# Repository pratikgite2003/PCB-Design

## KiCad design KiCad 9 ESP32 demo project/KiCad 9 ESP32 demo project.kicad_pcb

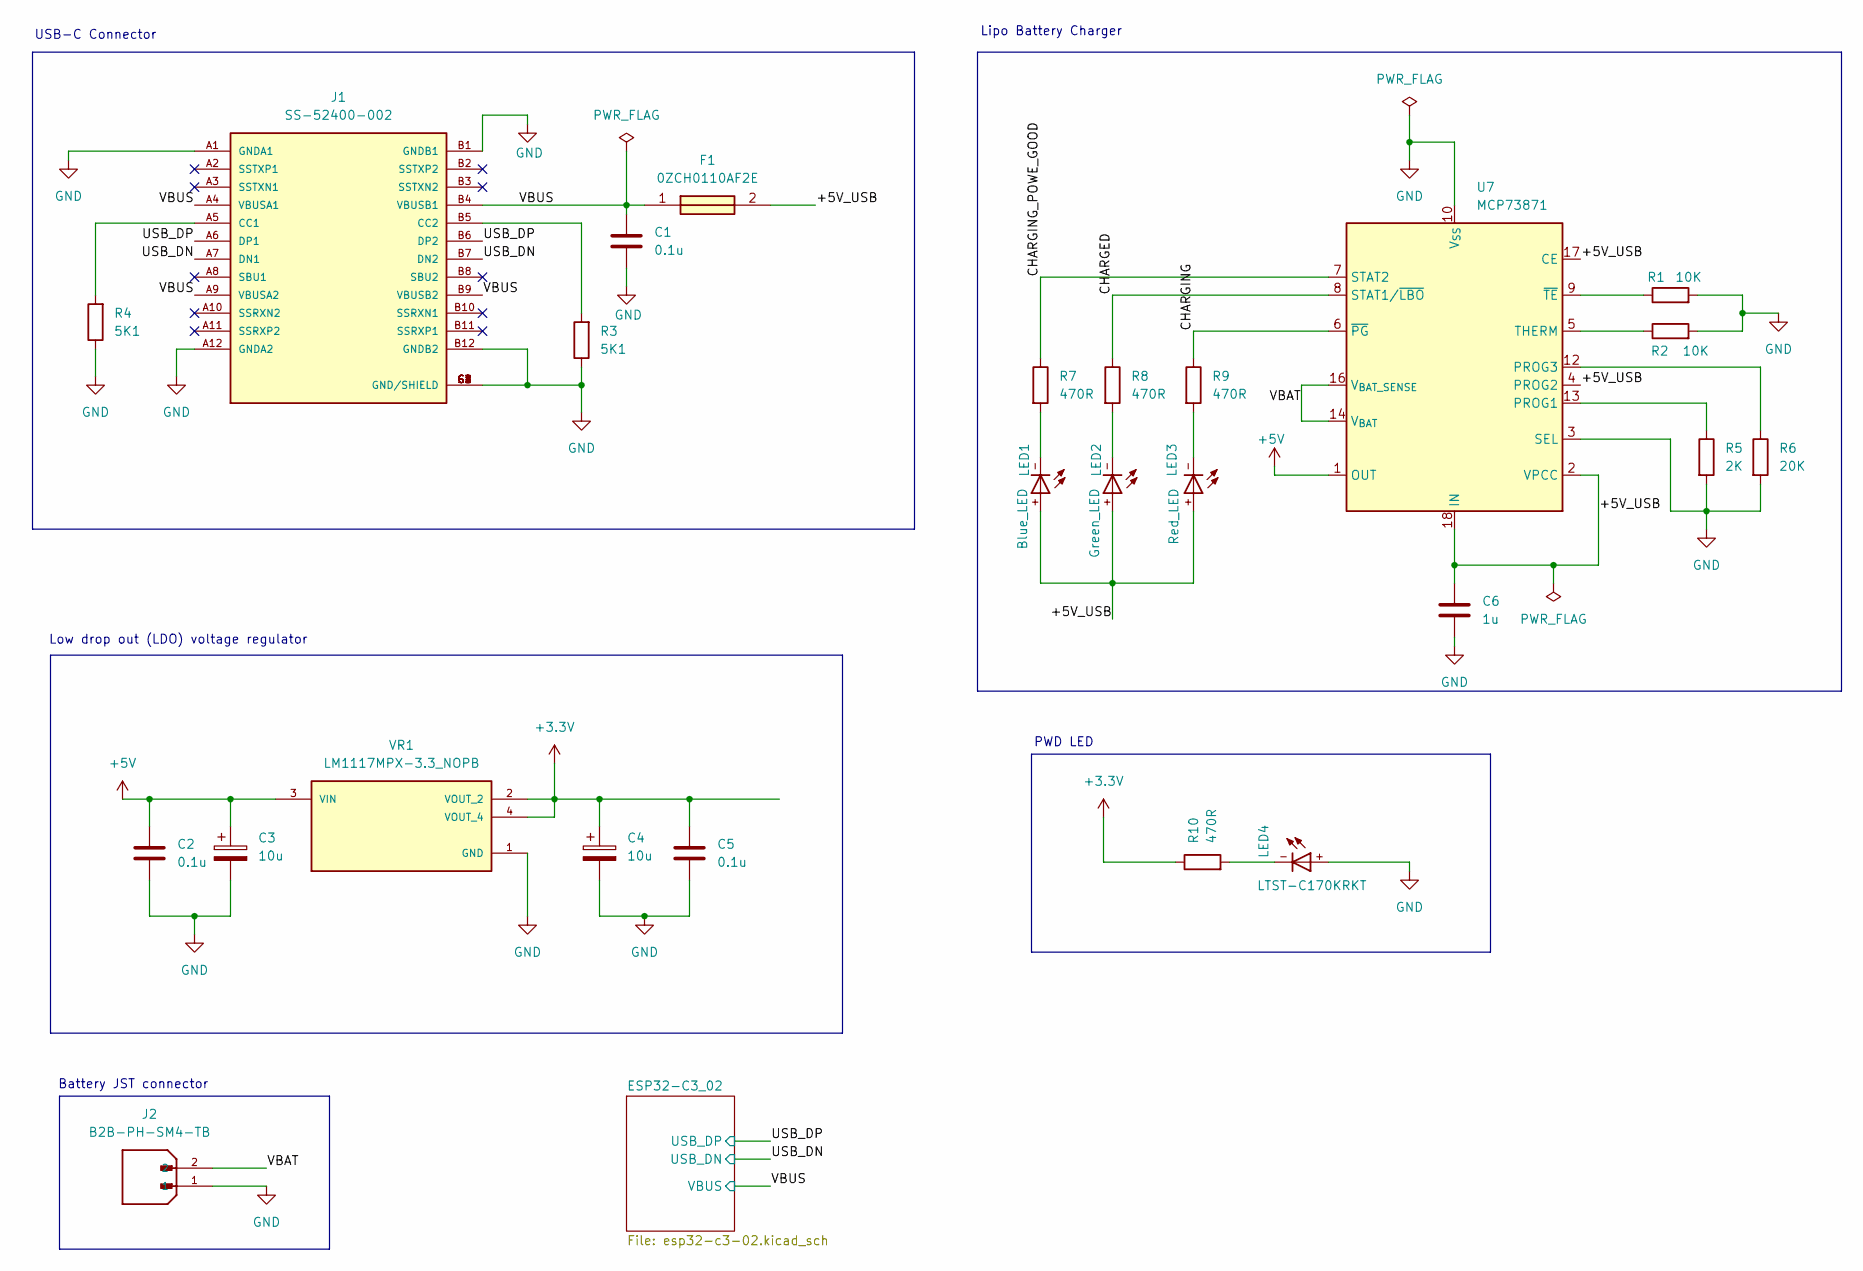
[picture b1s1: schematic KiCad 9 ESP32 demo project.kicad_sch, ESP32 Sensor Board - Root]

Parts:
C1, C2, C5: 0.1u; C_0805_2012Metric
C3, C4: 10u; CAPC3216X110N
C6: 1u; C_0805_2012Metric
F1: 0ZCH0110AF2E; FUSC3226X100N; Manufacturer_Part_Number 0ZCH0110AF2E
J1: SS-52400-002; BELFUSE_SS-52400-002; PARTREV A0
J2: B2B-PH-SM4-TB; JST_B2B-PH-SM4-TB; PARTREV N/A
LED1: Blue_LED; DIOC200X125X110
LED2: Green_LED; DIOC200X125X110
LED3: Red_LED; DIOC200X125X110
LED4: LTST-C170KRKT; DIOC200X125X110
R1, R2: 10K; R_0805_2012Metric
R3, R4: 5K1; R_0805_2012Metric
R5: 2K; R_0805_2012Metric
R6: 20K; R_0805_2012Metric
R7, R8, R9, R10: 470R; R_0805_2012Metric
U7: MCP73871; QFN-20-1EP_4x4mm_P0.5mm_EP2.5x2.5mm
VR1: LM1117MPX-3.3_NOPB; VREG_LM1117MPX-3.3_NOPB; PARTREV O

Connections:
+3.3V: C4.1, C5.1, R10.1, VR1.2 (VOUT_2), VR1.4 (VOUT_4); also elsewhere on the board
+5V: C2.1, C3.1, U7.1 (OUT), U7.20 (OUT), VR1.3 (VIN)
/+5V_USB: C6.1, F1.2, LED1.+, LED2.+, LED3.+, U7.2 (VPCC), U7.4 (PROG2), U7.17 (CE), U7.18 (IN), U7.19 (IN)
/CHARGED: R8.1, U7.8 (STAT1/~LBO)
/CHARGING: R9.1, U7.6 (~PG)
/CHARGING_POWE_GOOD: R7.1, U7.7 (STAT2)
/USB_DN: J1.A7 (DN1), J1.B7 (DN2); also elsewhere on the board
/USB_DP: J1.A6 (DP1), J1.B6 (DP2); also elsewhere on the board
/VBAT: J2.2, U7.14 (V_{BAT}), U7.15 (V_{BAT}), U7.16 (V_{BAT_SENSE})
/VBUS: C1.1, F1.1, J1.A4 (VBUSA1), J1.A9 (VBUSA2), J1.B4 (VBUSB1), J1.B9 (VBUSB2); also elsewhere on the board
GND: C1.2, C2.2, C3.2, C4.2, C5.2, C6.2, J1.A1 (GNDA1), J1.A12 (GNDA2), J1.B1 (GNDB1), J1.B12 (GNDB2), J1.G1 (GND/SHIELD), J1.G2 (GND/SHIELD), J1.G3 (GND/SHIELD), J1.G4 (GND/SHIELD), J1.S1 (GND/SHIELD), J1.S2 (GND/SHIELD), J1.S3 (GND/SHIELD), J1.S4 (GND/SHIELD), J2.1, LED4.+, R1.2, R2.2, R3.1, R4.1, R5.2, R6.2, U7.3 (SEL), U7.10 (V_{SS}), U7.11 (V_{SS}), U7.21 (V_{SS}), VR1.1 (GND); also elsewhere on the board
unnamed: J1.A5 (CC1), R4.2
unnamed: J1.B5 (CC2), R3.2
unnamed: LED1.-, R7.2
unnamed: LED2.-, R8.2
unnamed: LED3.-, R9.2
unnamed: LED4.-, R10.2
unnamed: R5.1, U7.13 (PROG1)
unnamed: R6.1, U7.12 (PROG3)
unnamed: R2.1, U7.5 (THERM)
unnamed: R1.1, U7.9 (~TE)

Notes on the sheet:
Lipo Battery Charger
Low drop out (LDO) voltage regulator
PWD LED
Battery JST connector
USB-C Connector

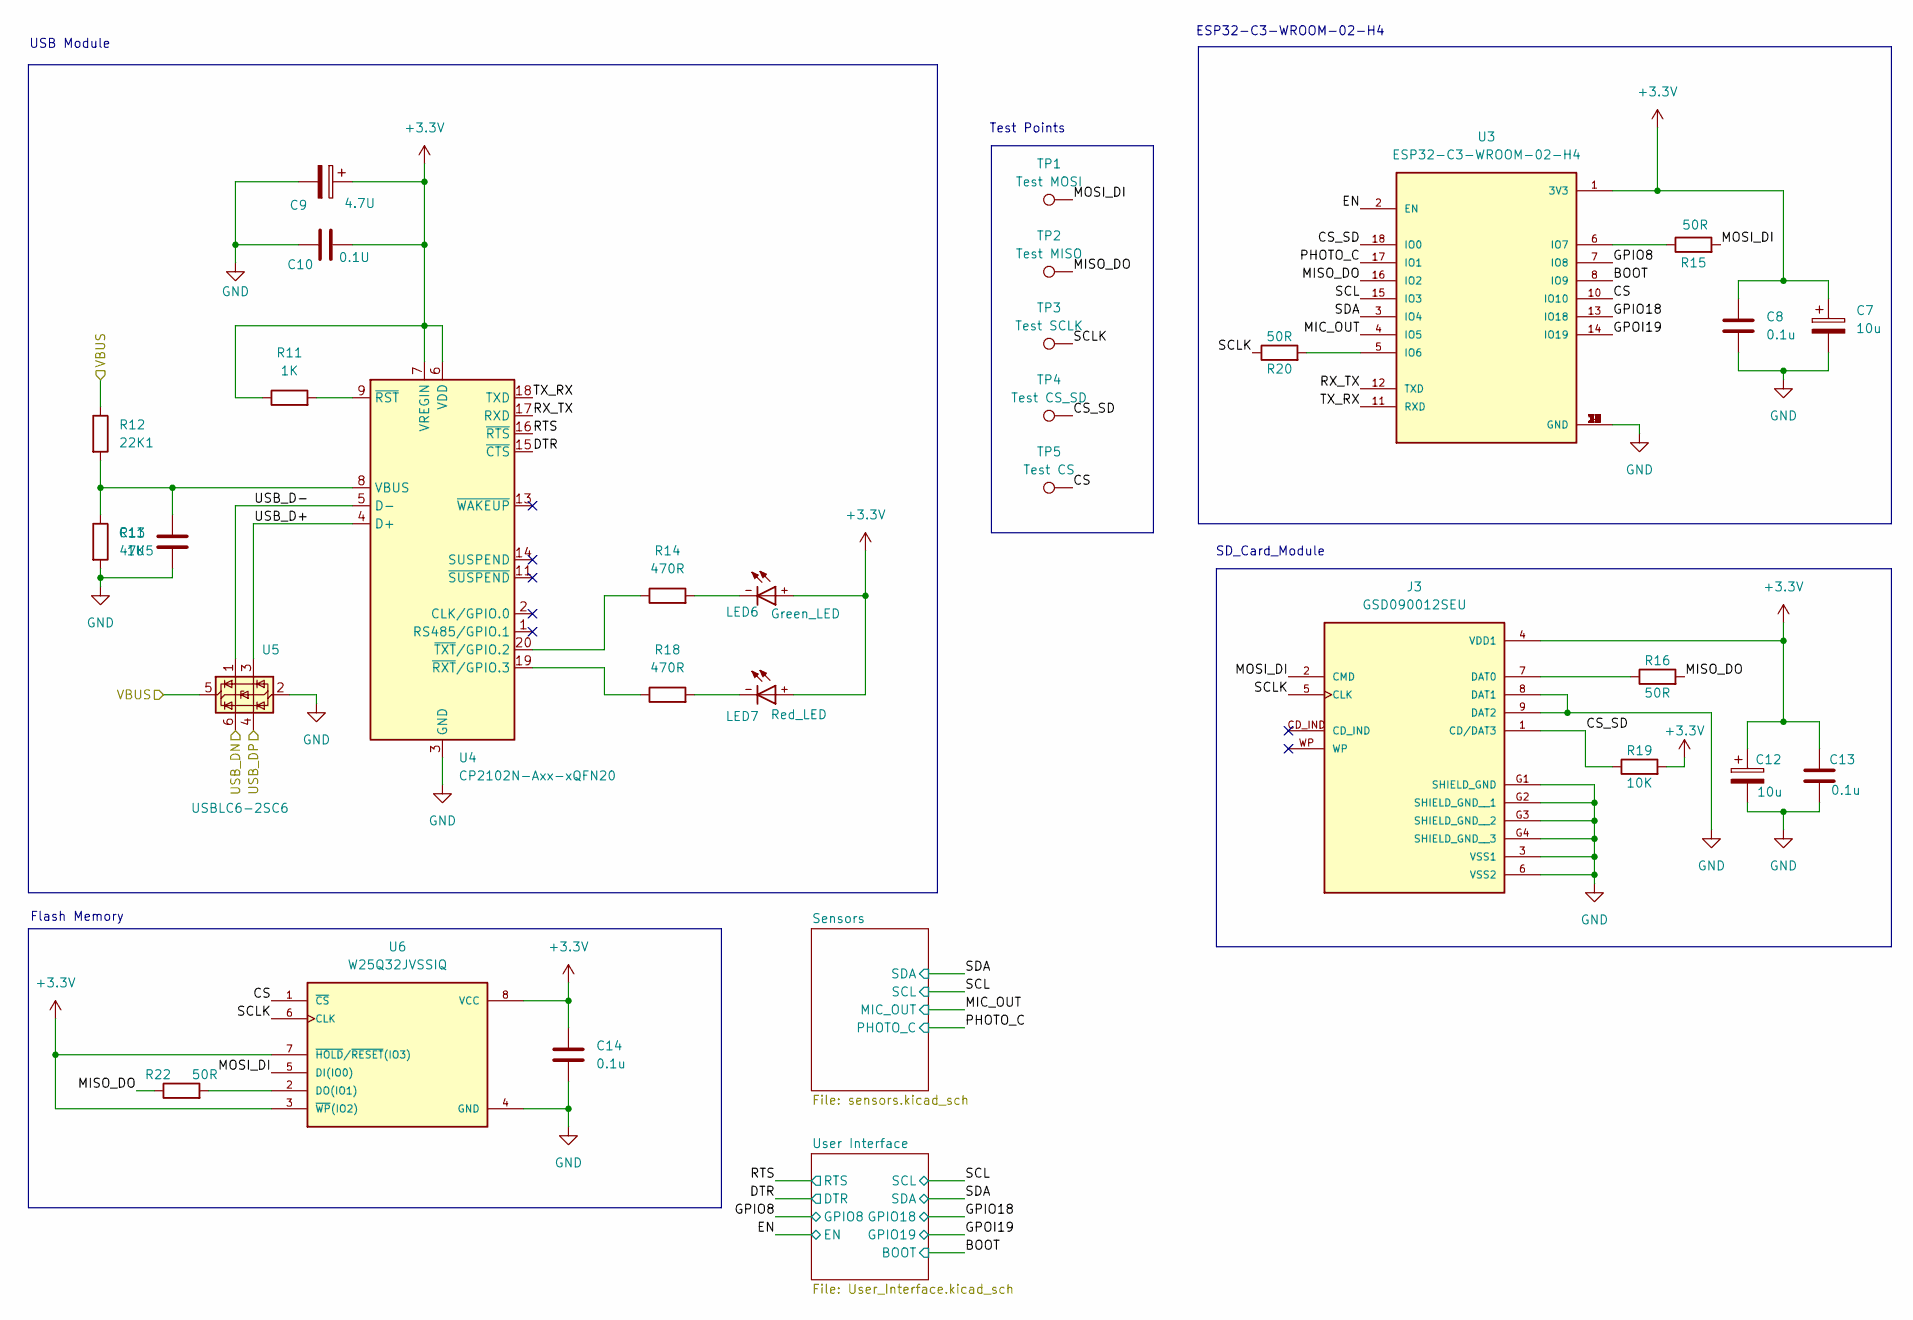
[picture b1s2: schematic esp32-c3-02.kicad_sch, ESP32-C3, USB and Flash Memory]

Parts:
C7: 10u; CAPC3216X110N
C8, C13, C14: 0.1u; C_0805_2012Metric
C9: 4.7U; CAPC3216X110N
C10: 0.1U; C_0805_2012Metric
C11: 1U; C_0805_2012Metric
C12: 10u; C_0805_2012Metric
J3: GSD090012SEU; AMPHENOL_GSD090012SEU; PARTREV E
LED6: Green_LED; DIOC200X125X110
LED7: Red_LED; DIOC200X125X110
R11: 1K; R_0805_2012Metric
R12: 22K1; R_0805_2012Metric
R13: 47K5; R_0805_2012Metric
R14, R18: 470R; R_0805_2012Metric
R15, R16, R20, R22: 50R; R_0805_2012Metric
R19: 10K; R_0805_2012Metric
TP1: Test MOSI; TestPoint_Pad_D1.0mm
TP2: Test MISO; TestPoint_Pad_D1.0mm
TP3: Test SCLK; TestPoint_Pad_D1.0mm
TP4: Test CS_SD; TestPoint_Pad_D1.0mm
TP5: Test CS; TestPoint_Pad_D1.0mm
U3: ESP32-C3-WROOM-02-H4; MODULE_ESP32-C3-WROOM-02-H4
U4: CP2102N-Axx-xQFN20; SiliconLabs_QFN-20-1EP_3x3mm_P0.5mm_EP1.8x1.8mm
U5: USBLC6-2SC6; SOT-23-6
U6: W25Q32JVSSIQ; SOIC127P790X216-8N; M_PART_NUMBER W25QXX

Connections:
+3.3V: C7.1, C8.1, C9.1, C10.2, C12.1, C13.1, C14.1, J3.4 (VDD1), LED6.+, LED7.+, R11.1, R19.2, U3.1 (3V3), U4.6 (VDD), U4.7 (VREGIN), U6.3 (~WP(IO2)), U6.7 (~HOLD/~RESET(IO3)), U6.8 (VCC); also elsewhere on the board
/ESP32-C3_02/BOOT: U3.8 (IO9); also elsewhere on the board
/ESP32-C3_02/CS: TP5.1, U3.10 (IO10), U6.1 (~CS)
/ESP32-C3_02/CS_SD: J3.1 (CD/DAT3), R19.1, TP4.1, U3.18 (IO0)
/ESP32-C3_02/DTR: U4.15 (~CTS); also elsewhere on the board
/ESP32-C3_02/EN: U3.2 (EN); also elsewhere on the board
/ESP32-C3_02/GPIO8: U3.7 (IO8); also elsewhere on the board
/ESP32-C3_02/GPIO18: U3.13 (IO18); also elsewhere on the board
/ESP32-C3_02/GPOI19: U3.14 (IO19); also elsewhere on the board
/ESP32-C3_02/MIC_OUT: U3.4 (IO5); also elsewhere on the board
/ESP32-C3_02/MISO_DO: R16.2, R22.1, TP2.1, U3.16 (IO2)
/ESP32-C3_02/MOSI_DI: J3.2 (CMD), R15.2, TP1.1, U6.5 (DI(IO0))
/ESP32-C3_02/PHOTO_C: U3.17 (IO1); also elsewhere on the board
/ESP32-C3_02/RTS: U4.16 (~RTS); also elsewhere on the board
/ESP32-C3_02/RX_TX: U3.12 (TXD), U4.17 (RXD)
/ESP32-C3_02/SCL: U3.15 (IO3); also elsewhere on the board
/ESP32-C3_02/SCLK: J3.5 (CLK), R20.1, TP3.1, U6.6 (CLK)
/ESP32-C3_02/SDA: U3.3 (IO4); also elsewhere on the board
/ESP32-C3_02/TX_RX: U3.11 (RXD), U4.18 (TXD)
/ESP32-C3_02/USB_D+: U4.4 (D+), U5.3 (I/O2)
/ESP32-C3_02/USB_D-: U4.5 (D-), U5.1 (I/O1)
/USB_DN: U5.6 (I/O1); also elsewhere on the board
/USB_DP: U5.4 (I/O2); also elsewhere on the board
/VBUS: R12.1, U5.5 (VBUS); also elsewhere on the board
GND: C7.2, C8.2, C9.2, C10.1, C11.2, C12.2, C13.2, C14.2, J3.3 (VSS1), J3.6 (VSS2), J3.8 (DAT1), J3.9 (DAT2), J3.G1 (SHIELD_GND), J3.G2 (SHIELD_GND__1), J3.G3 (SHIELD_GND__2), J3.G4 (SHIELD_GND__3), R13.2, U3.9 (GND), U3.19 (GND), U3.20 (GND), U3.21 (GND), U3.22 (GND), U3.23 (GND), U3.24 (GND), U3.25 (GND), U3.26 (GND), U3.27 (GND), U3.28 (GND), U3.29 (GND), U3.30 (GND), U3.31 (GND), U3.32 (GND), U3.33 (GND), U3.34 (GND), U3.35 (GND), U3.36 (GND), U3.37 (GND), U3.38 (GND), U3.39 (GND), U4.3 (GND), U4.12 (GND), U4.21 (GND), U5.2 (GND), U6.4 (GND); also elsewhere on the board
unnamed: J3.7 (DAT0), R16.1
unnamed: LED6.-, R14.2
unnamed: LED7.-, R18.2
unnamed: R20.2, U3.5 (IO6)
unnamed: R15.1, U3.6 (IO7)
unnamed: C11.1, R12.2, R13.1, U4.8 (VBUS)
unnamed: R11.2, U4.9 (~RST)
unnamed: R18.1, U4.19 (~RXT/GPIO.3)
unnamed: R14.1, U4.20 (~TXT/GPIO.2)
unnamed: R22.2, U6.2 (DO(IO1))

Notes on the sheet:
Test Points
USB Module
Flash Memory
ESP32-C3-WROOM-02-H4
SD_Card_Module

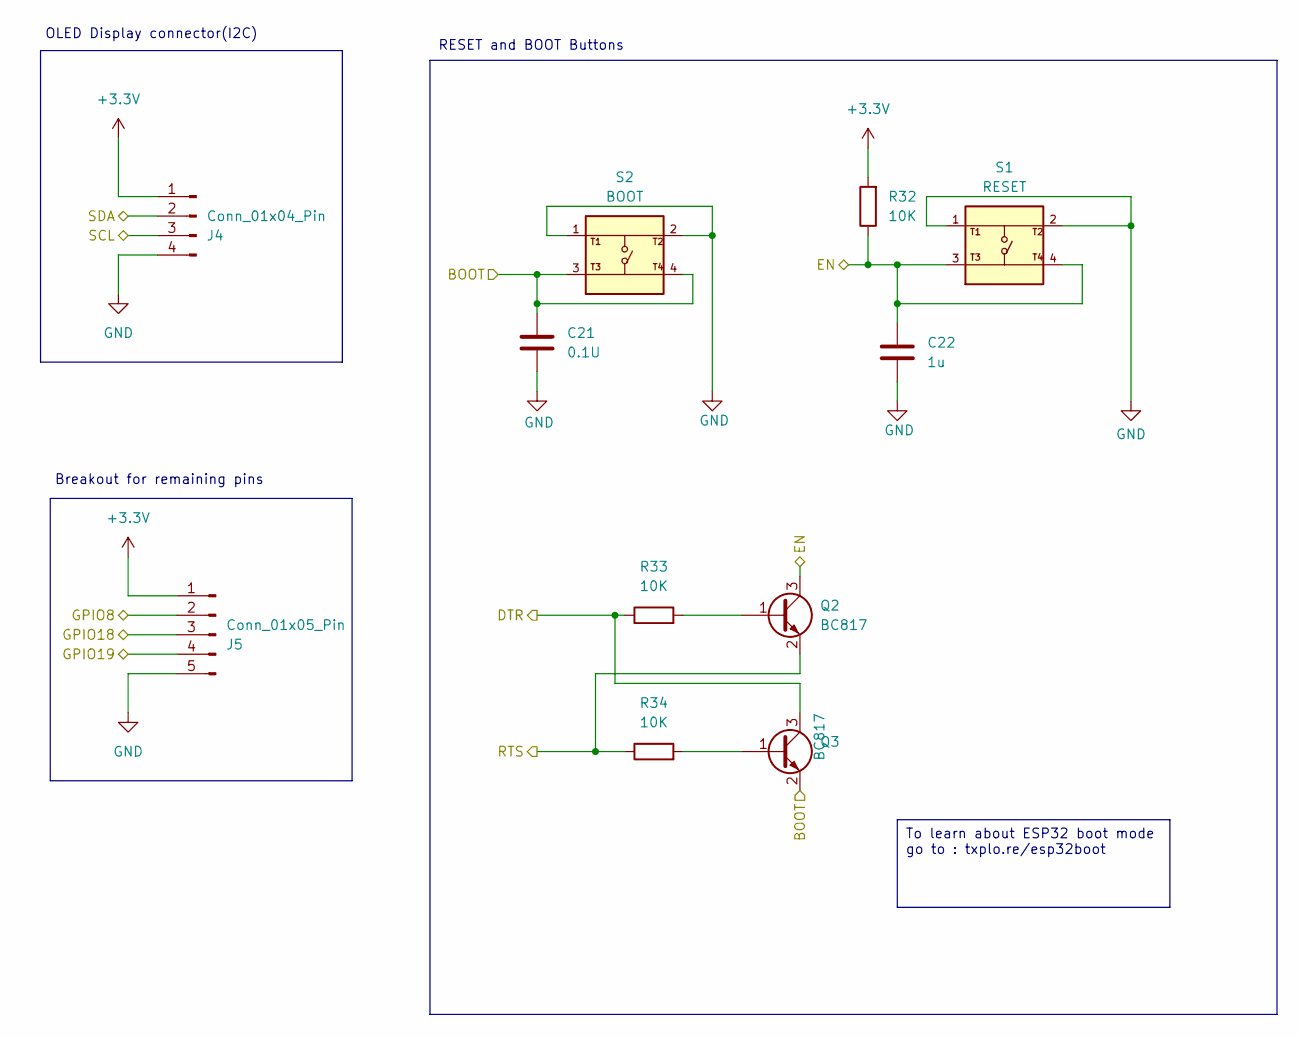
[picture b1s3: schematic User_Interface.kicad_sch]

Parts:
C21: 0.1U; C_0805_2012Metric
C22: 1u; C_0805_2012Metric
J4: Conn_01x04_Pin; PinHeader_1x04_P2.54mm_Vertical
J5: Conn_01x05_Pin; PinHeader_1x05_P2.54mm_Vertical
Q2, Q3: BC817; SOT95P230X110-3N
R32, R33, R34: 10K; R_0805_2012Metric
S1: RESET; SW_USLPT2819DT2TR; PARTREV P
S2: BOOT; SW_USLPT2819DT2TR; PARTREV P

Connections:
+3.3V: J4.1, J5.1, R32.2; also elsewhere on the board
/ESP32-C3_02/BOOT: C21.1, Q3.2 (E), S2.3, S2.4; also elsewhere on the board
/ESP32-C3_02/DTR: Q3.3 (C), R33.1; also elsewhere on the board
/ESP32-C3_02/EN: C22.1, Q2.3 (C), R32.1, S1.3, S1.4; also elsewhere on the board
/ESP32-C3_02/GPIO8: J5.2; also elsewhere on the board
/ESP32-C3_02/GPIO18: J5.3; also elsewhere on the board
/ESP32-C3_02/GPOI19: J5.4; also elsewhere on the board
/ESP32-C3_02/RTS: Q2.2 (E), R34.1; also elsewhere on the board
/ESP32-C3_02/SCL: J4.3; also elsewhere on the board
/ESP32-C3_02/SDA: J4.2; also elsewhere on the board
GND: C21.2, C22.2, J4.4, J5.5, S1.1, S1.2, S2.1, S2.2; also elsewhere on the board
unnamed: Q2.1 (B), R33.2
unnamed: Q3.1 (B), R34.2

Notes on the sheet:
To learn about ESP32 boot mode go to : txplo.re/esp32boot
Breakout for remaining pins
RESET and BOOT Buttons
OLED Display connector(I2C)

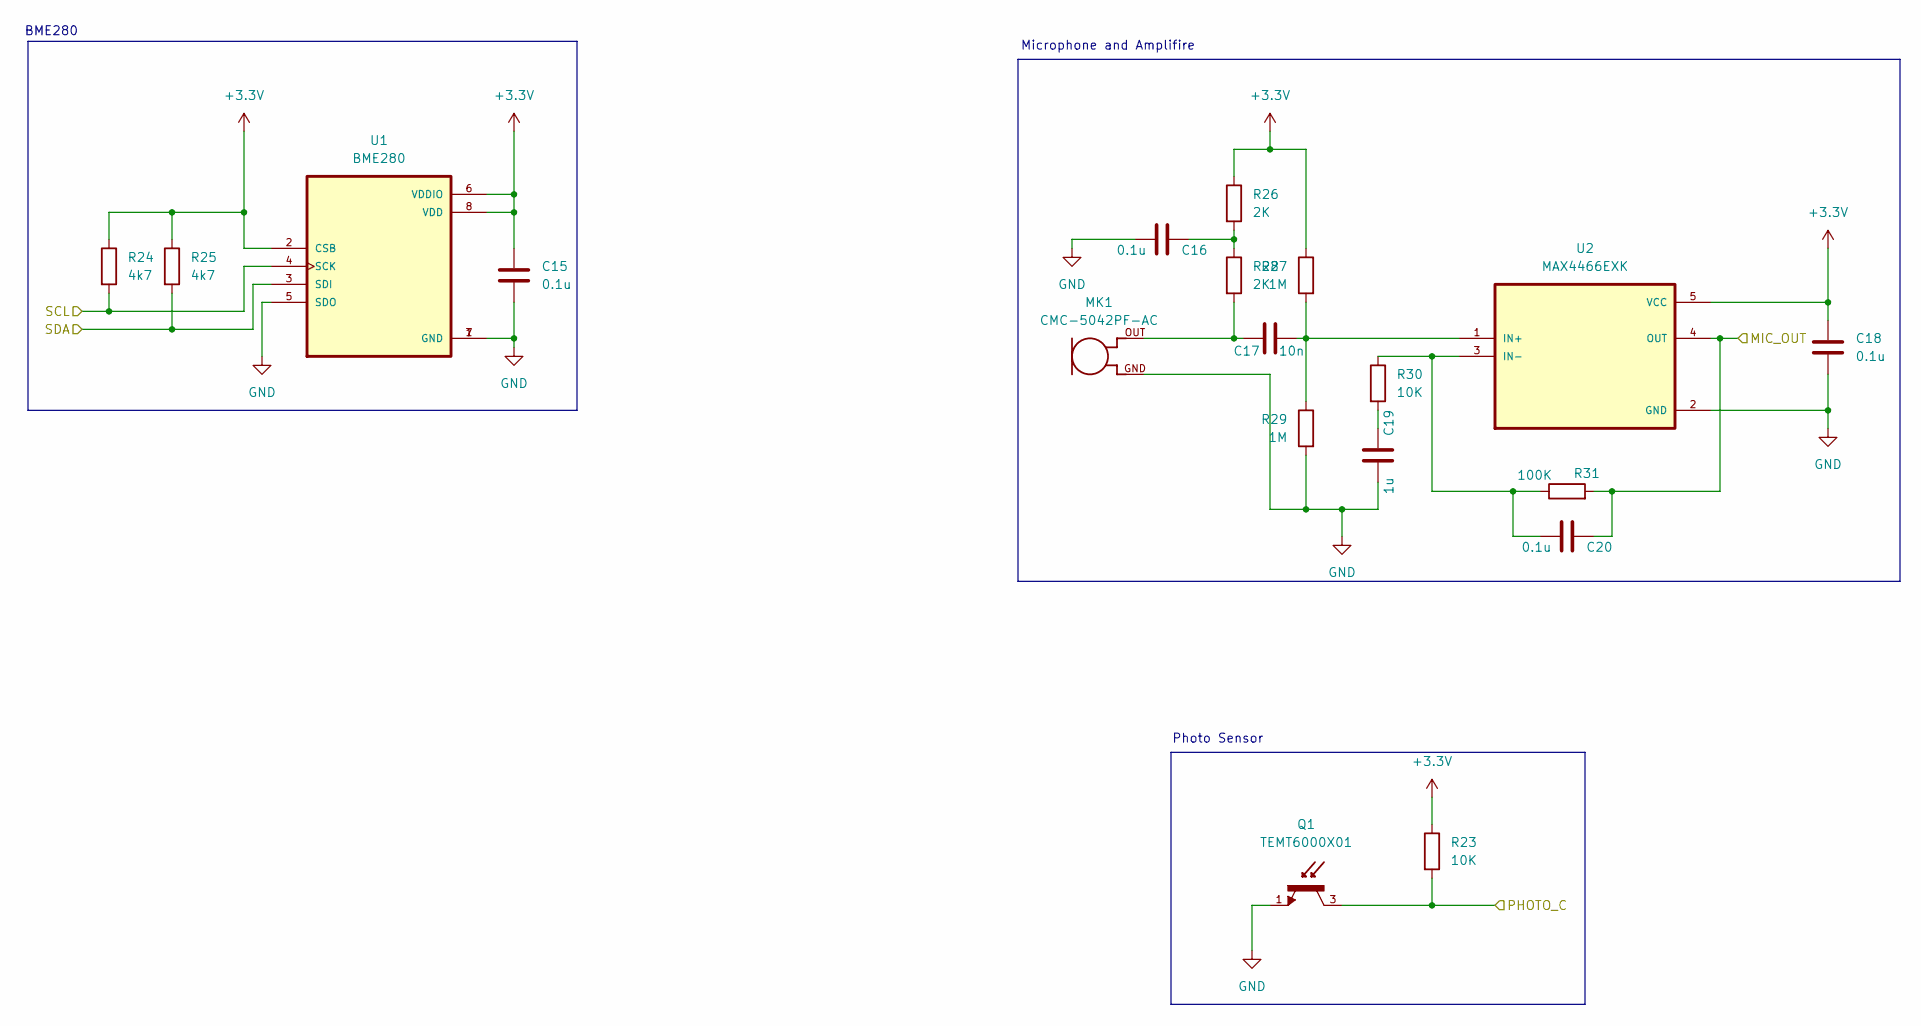
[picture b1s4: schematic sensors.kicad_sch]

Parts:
C15, C16, C18, C20: 0.1u; C_0805_2012Metric
C17: 10n; C_0805_2012Metric
C19: 1u; C_0805_2012Metric
MK1: CMC-5042PF-AC; CUI_CMC-5042PF-AC
Q1: TEMT6000X01; TRANS_TEMT6000X01; PARTREV 1.9
R23, R30: 10K; R_0805_2012Metric
R24, R25: 4k7; R_0805_2012Metric
R26, R28: 2K; R_0805_2012Metric
R27, R29: 1M; R_0805_2012Metric
R31: 100K; R_0805_2012Metric
U1: BME280; PSON65P250X250X100-8N
U2: MAX4466EXK; SOT65P210X110-5N

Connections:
+3.3V: C15.1, C18.1, R23.1, R24.1, R25.1, R26.1, R27.1, U1.2 (CSB), U1.6 (VDDIO), U1.8 (VDD), U2.5 (VCC); also elsewhere on the board
/ESP32-C3_02/MIC_OUT: C20.2, R31.2, U2.4 (OUT); also elsewhere on the board
/ESP32-C3_02/PHOTO_C: Q1.3, R23.2; also elsewhere on the board
/ESP32-C3_02/SCL: R24.2, U1.4 (SCK); also elsewhere on the board
/ESP32-C3_02/SDA: R25.2, U1.3 (SDI); also elsewhere on the board
GND: C15.2, C16.1, C18.2, C19.1, MK1.GND, Q1.1, R29.2, U1.1 (GND), U1.5 (SDO), U1.7 (GND), U2.2 (GND); also elsewhere on the board
unnamed: C16.2, R26.2, R28.1
unnamed: C17.2, MK1.OUT, R28.2
unnamed: C19.2, R30.2
unnamed: C17.1, R27.2, R29.1, U2.1 (IN+)
unnamed: C20.1, R30.1, R31.1, U2.3 (IN-)

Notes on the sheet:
Microphone and Amplifire
Photo Sensor
BME280

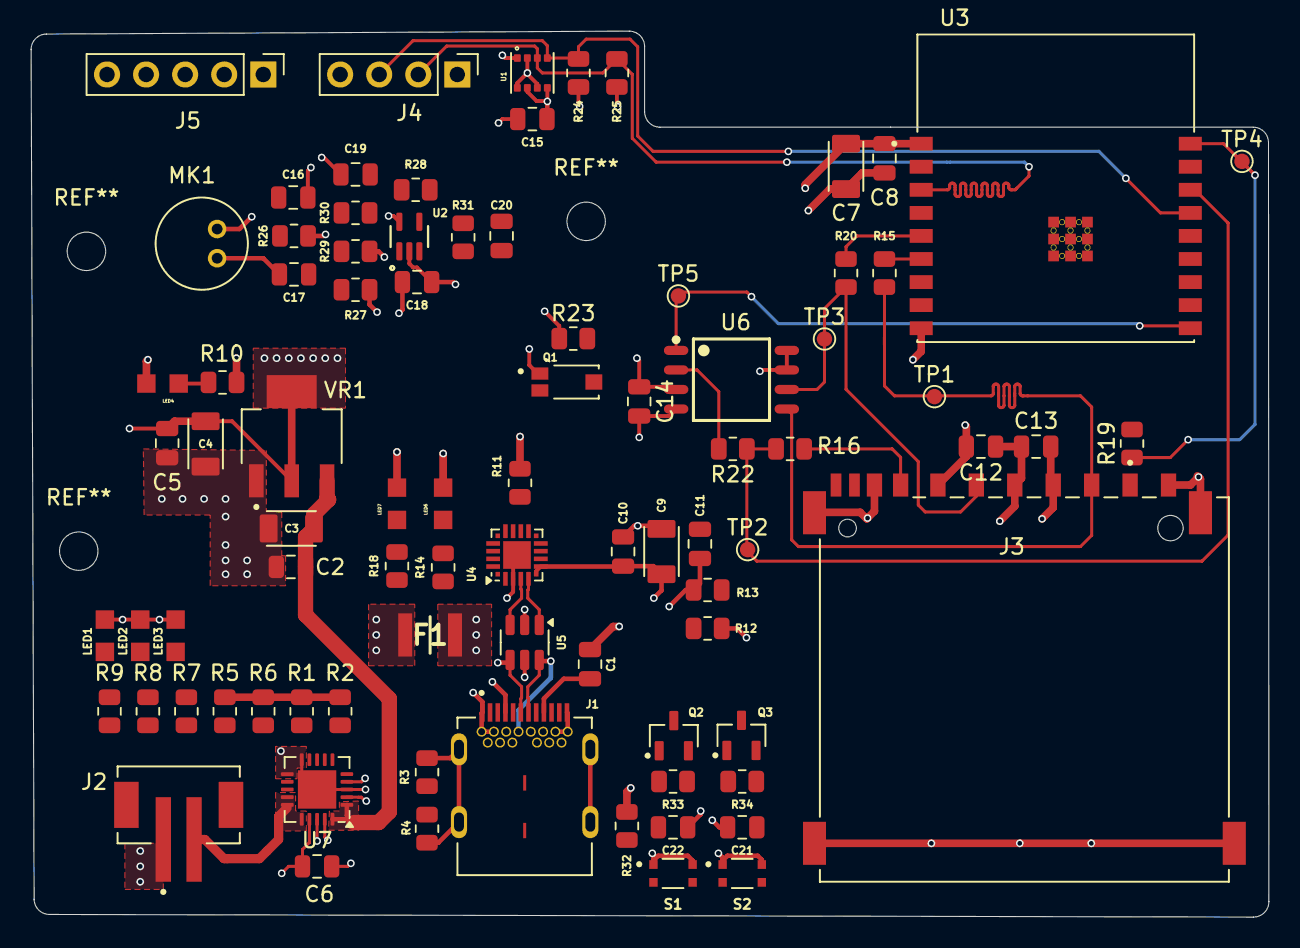
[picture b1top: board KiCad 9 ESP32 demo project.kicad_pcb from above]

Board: 4 copper layers, 80.5 x 57.6 mm, 85 parts (0 on the bottom side), 58 nets.

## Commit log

2025-03-03 Check
2025-03-04 schematic esp32 sheet
2025-03-04 schematic esp32 done
2025-03-04 Schematic Done
2025-03-05 Ignored PCB-Design submodule
2025-03-05 stated layout
2025-03-06 checking working from lp
2025-03-06 power layout done
